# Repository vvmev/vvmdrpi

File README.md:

# VVM Digital I/O Raspberry Pi Hat

This hat provides power to the Raspberry Pi through a generic MP1584 DC/DC converter, the bus connector with supplies and I2C, and an optional WS2812.

The Raspberry Pi hat schematic and layout is based on [Xesscorp's RPi Hat Template](https://github.com/xesscorp/RPi_Hat_Template).

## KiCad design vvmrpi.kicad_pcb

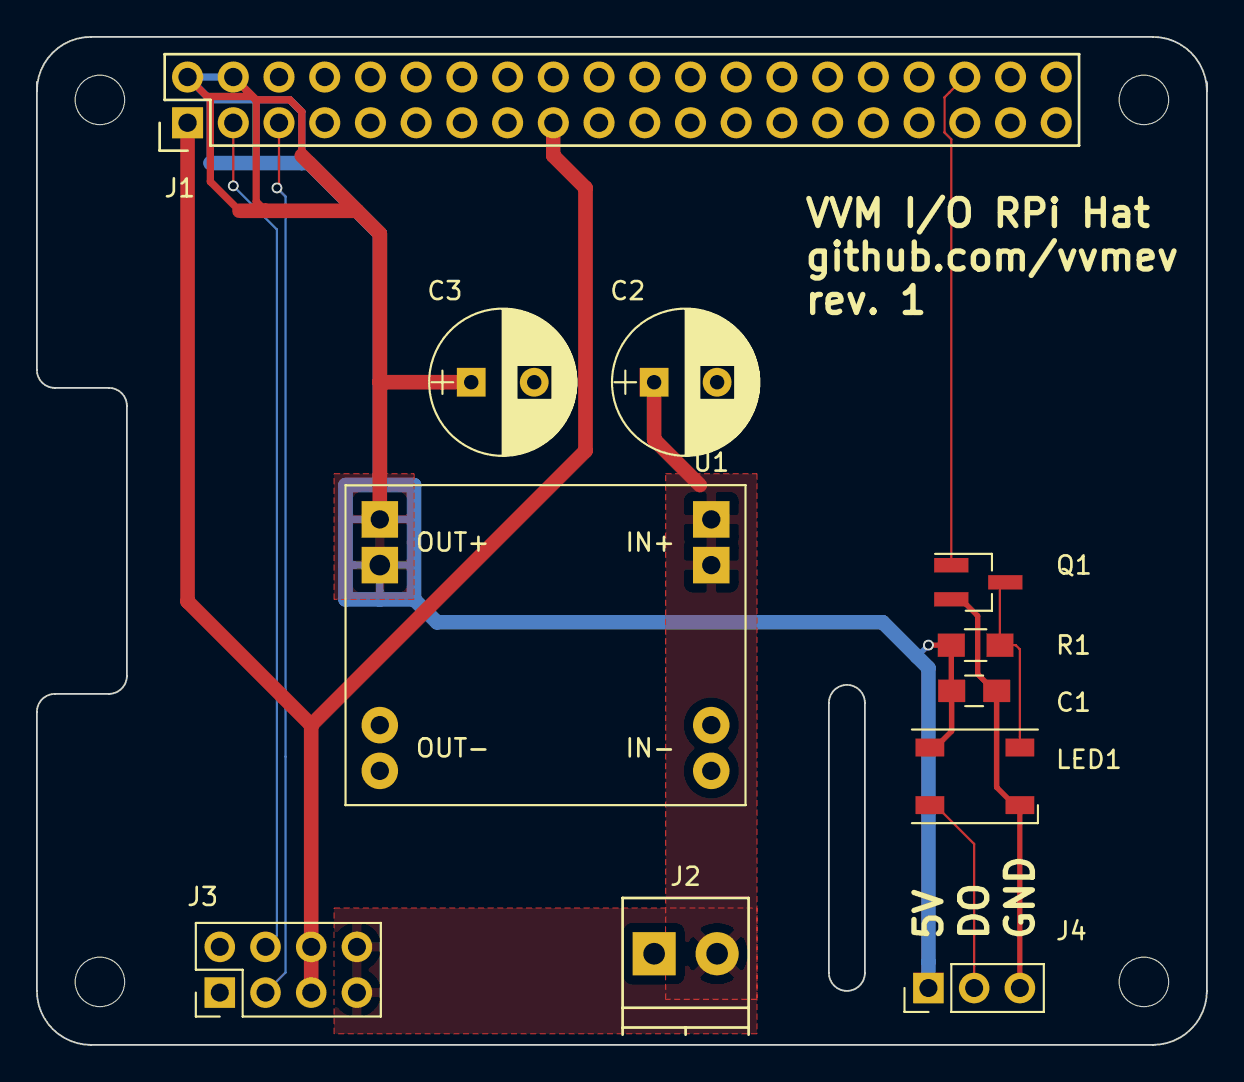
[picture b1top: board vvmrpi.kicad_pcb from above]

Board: 2 copper layers, 65.0 x 56.0 mm, 11 parts (0 on the bottom side), 9 nets.

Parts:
C1: 100n; C_0805_HandSoldering
C2, C3: 100u; CP_Radial_D8.0mm_P3.50mm
J1: RPi_GPIO; Pin_Header_Straight_2x20
J2: Conn_01x02; TerminalBlock_Phoenix_PT-3.5mm_2pol
J3: Conn_02x04_Odd_Even; Pin_Header_Straight_2x04_Pitch2.54mm
J4: Conn_01x03; Pin_Header_Straight_1x03_Pitch2.54mm
LED1: WS2812B; LED_WS2812B-PLCC4
Q1: Si2303DS; SOT-23_Handsoldering
R1: 10k; R_0805_HandSoldering
U1: MP1584EN-module; MP1584mod

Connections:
+3V3: J1.1, J1.17, J3.5, J3.6
+5V: C1.1, C3.1, J1.2, J1.4, J4.1, LED1.1, R1.1, U1.5, U1.6
+12V: C2.1, J2.2, J3.7, J3.8, U1.1, U1.2
/RPi_GPIO/LED_DIN: LED1.4, Q1.3, R1.2
/RPi_GPIO/LED_DOUT: J4.2, LED1.2
/RPi_GPIO/PWM0: J1.36, Q1.1
/RPi_GPIO/SCL: J1.5, J3.3
/RPi_GPIO/SDA: J1.3, J3.4
GND: C1.2, C2.2, C3.2, J1.6, J1.9, J1.14, J1.20, J1.25, J1.30, J1.34, J1.39, J2.1, J3.1, J3.2, J4.3, LED1.3, Q1.2, U1.3, U1.4, U1.7, U1.8

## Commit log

2019-05-05 First version
2019-05-05 Small corrections
